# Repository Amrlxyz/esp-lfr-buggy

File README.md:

# ESP Line Following Robot

**GROUP 48:** 2nd Year Embedded Systems Project (ESP) 2023/24.

Project is in collaboration with 5 teammates: 
- [@Amrlxyz (me)](https://github.com/Amrlxyz) : Main Programmer + 3D CAD Designer 
- [@Hubr1z](https://github.com/Hubr1z) : 2nd Programmer
- [@Sarahelma](https://github.com/Sarahelma) : PCB Designer
- [@nishoujiwojiubuhuine](https://github.com/nishoujiwojiubuhuine) : 3rd Programmer + General Tech 
- [@Giselle-zheng](https://github.com/Giselle-zheng) : Wiring and Electrical

## Gallery

*Buggy Picture on the final race day*

*Final Buggy Render Using SolidWorks*

## Achievements

- **ESP 2023/24 Final Race Winner !!!**
- 100% for TDA (Techincal Demonstration A)
- 100% for TDB (Techincal Demonstration B)
- 100% for TDC (Techincal Demonstration C)

## Features

- Mbed v5.15
- Nucleo STM32F401RE 
- Custom Sensor Array PCB
- Array of 6x TCRT5000 IR sensor for line following
- Custom CAD Model Designed in Solidworks

## API Documentation

Link to documentation: [Github Pages](https://amrlxyz.github.io/esp-lfr-buggy/)

## How to Use

### Flashing the MCU

1. Use the wiring diagram to connect the components.
2. Clone the project directly to Keil Studio Cloud.
3. Compile and flash on to the microcontroller.
4. Control the buggy using Bluetooth commands.

### How to run

1. Connect BLE to a phone
2. Place the whole sensor array in the black area of the track
3. Send "calibrate" Command
4. Wait until message is recieved on the phone
5. Place the buggy in the middle of the line
6. Send "line_follow" Command

## Buggy Commands

### Setup

1. Use "Serial Bluetooth Terminal" app on Android
2. Settings -> Send -> Newline -> None
3. Send Commands

### Command Format 

[2/3 Capital Letters] [optional value for certain commands] ['/' -> end character]

Full command list is in main.cpp

__Examples:__

EC/ -> "Execute" "Calibrate"

EF/ -> "Execute" "line_follow"

GSB/ -> Get the speed of both motors

## Linkedin Article

[Article Link](https://www.linkedin.com/pulse/2nd-year-embedded-systems-project-final-race-winner-hakeem-jfuzf)

I might have mentioned a follow-up technical write-up at the end... but life (and distractions) keep happening. We'll see.

## Hello Future UoM 2nd Yr EEE Students

Feel free to use this code as inspiration (at your own risk). Looking back, definitely there are ways to improve it.

If you find the code helpful, feel free to drop a star ⭐ on the repo _(I crave external validation)_

Goodluck!

## Dependencies

Imported 3rd Party Mbed Libraries

- [Driver Board Onboard Battery Monitor](https://os.mbed.com/users/EmbeddedSam/code/Nucleo_F401RE_DS271_Battery_Monitor/) by Sam Walsh
- [QEI Library](https://os.mbed.com/cookbook/QEI) by Aron Berk

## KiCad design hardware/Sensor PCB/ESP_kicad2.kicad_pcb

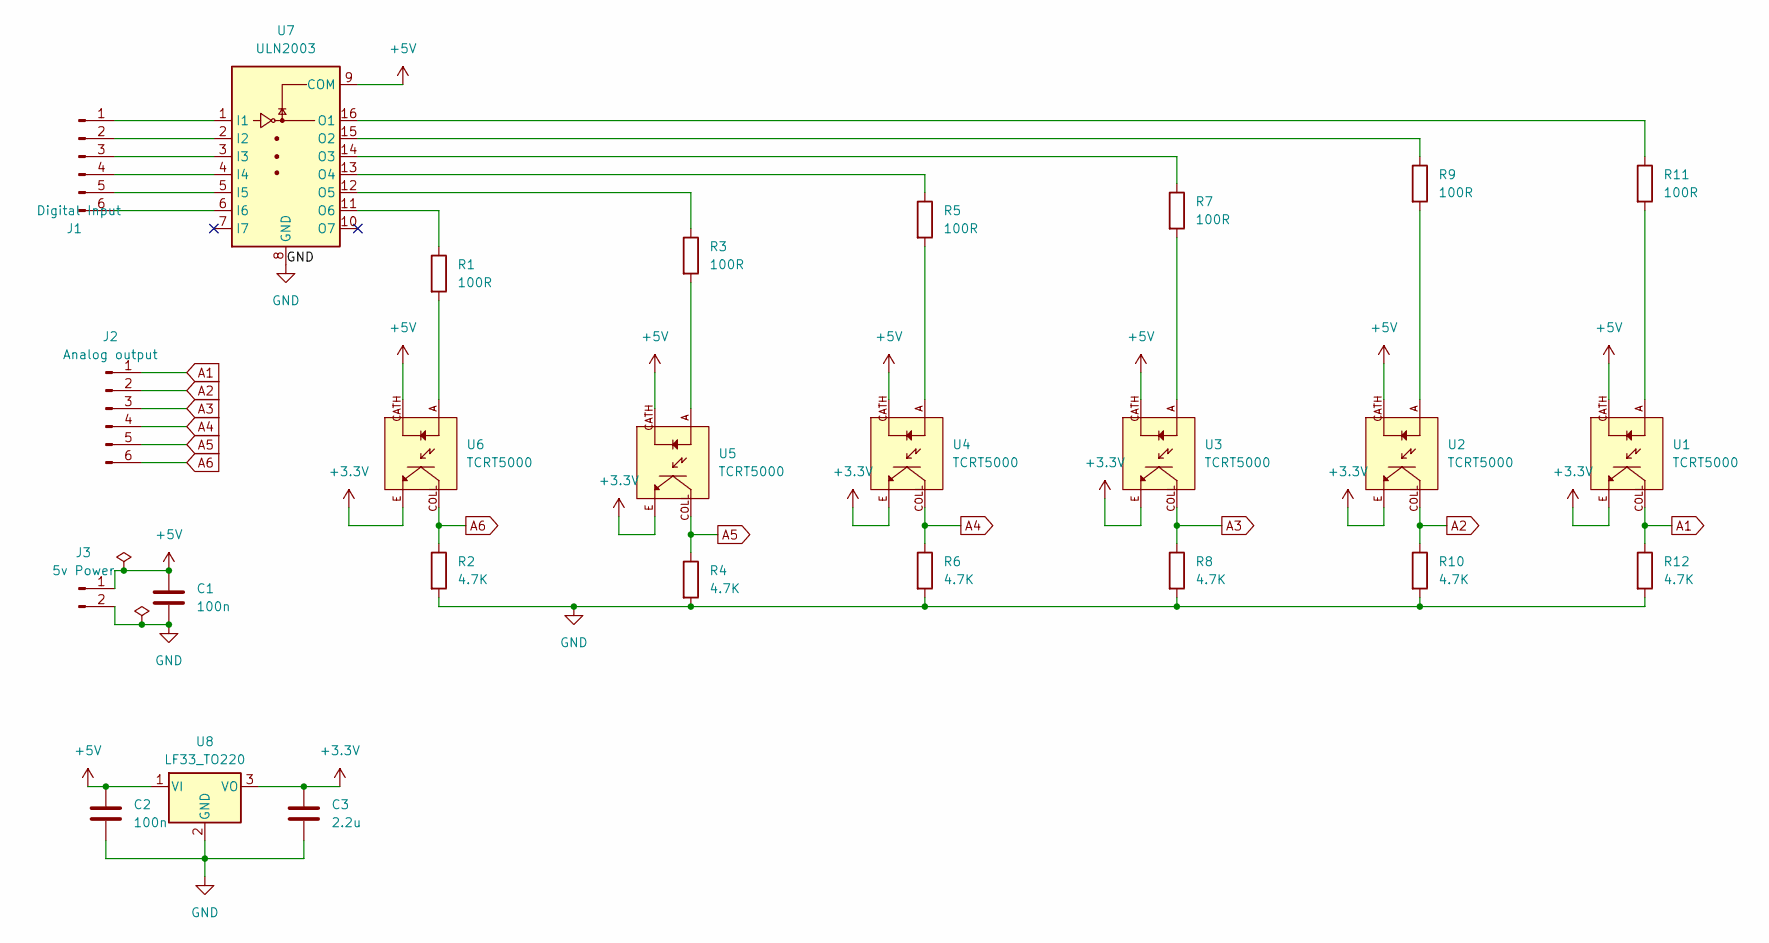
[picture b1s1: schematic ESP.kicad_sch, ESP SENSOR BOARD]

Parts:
C1, C2: 100n; CP_Radial_D5.0mm_P2.50mm
C3: 2.2u; CP_Radial_D5.0mm_P2.50mm
J1: Digital Input; JST_EH_B6B-EH-A_1x06_P2.50mm_Vertical
J2: Analog output; JST_EH_B6B-EH-A_1x06_P2.50mm_Vertical
J3: 5v Power; JST_ACH_BM02B-ACHSS-GAN-ETF_1x02-1MP_P1.20mm_Vertical
R1, R3, R5, R7, R9: 100R; R_Axial_DIN0207_L6.3mm_D2.5mm_P7.62mm_Horizontal
R2, R4, R6, R8, R10, R12: 4.7K; R_Axial_DIN0207_L6.3mm_D2.5mm_P7.62mm_Horizontal
R11: 100R; R_Axial_DIN0207_L6.3mm_D2.5mm_P5.08mm_Vertical
U1, U2, U3, U4, U5, U6: TCRT5000; OPTO_TCRT5000; PARTREV 1.7
U7: ULN2003; DIP-16_W7.62mm
U8: LF33_TO220; TO-220-3_Vertical

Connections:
+3.3V: C3.1, U1.E, U2.E, U3.E, U4.E, U5.E, U6.E, U8.3 (VO)
+5V: C1.1, C2.1, J3.1, U1.CATH, U2.CATH, U3.CATH, U4.CATH, U5.CATH, U6.CATH, U7.9 (COM), U8.1 (VI)
A1: J2.1, R12.1, U1.COLL
A2: J2.2, R10.1, U2.COLL
A3: J2.3, R8.1, U3.COLL
A4: J2.4, R6.1, U4.COLL
A5: J2.5, R4.1, U5.COLL
A6: J2.6, R2.1, U6.COLL
GND: C1.2, C2.2, C3.2, J3.2, R2.2, R4.2, R6.2, R8.2, R10.2, R12.2, U7.8 (GND), U8.2 (GND)
unnamed: J1.1, U7.1 (I1)
unnamed: J1.2, U7.2 (I2)
unnamed: J1.3, U7.3 (I3)
unnamed: J1.4, U7.4 (I4)
unnamed: J1.5, U7.5 (I5)
unnamed: J1.6, U7.6 (I6)
unnamed: R1.2, U6.A
unnamed: R3.2, U5.A
unnamed: R5.2, U4.A
unnamed: R7.2, U3.A
unnamed: R9.2, U2.A
unnamed: R11.2, U1.A
unnamed: R11.1, U7.16 (O1)
unnamed: R9.1, U7.15 (O2)
unnamed: R7.1, U7.14 (O3)
unnamed: R5.1, U7.13 (O4)
unnamed: R3.1, U7.12 (O5)
unnamed: R1.1, U7.11 (O6)

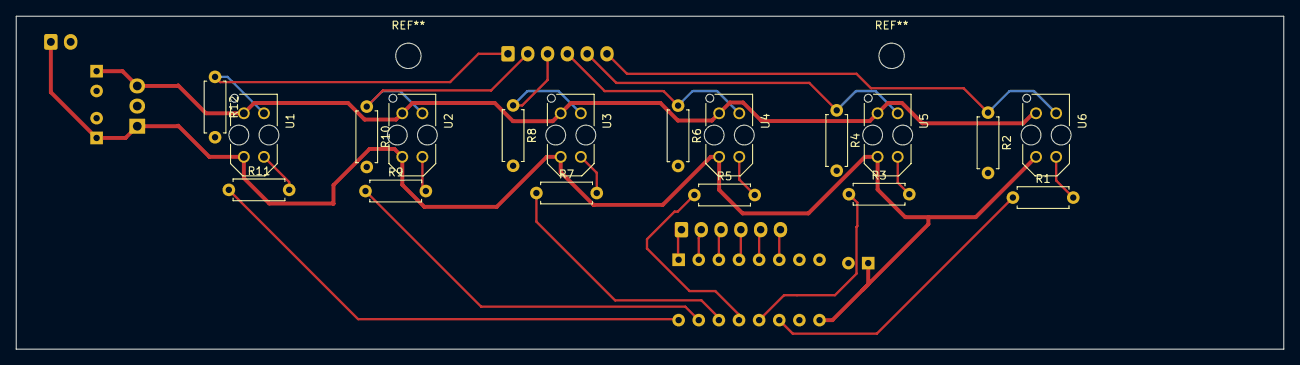
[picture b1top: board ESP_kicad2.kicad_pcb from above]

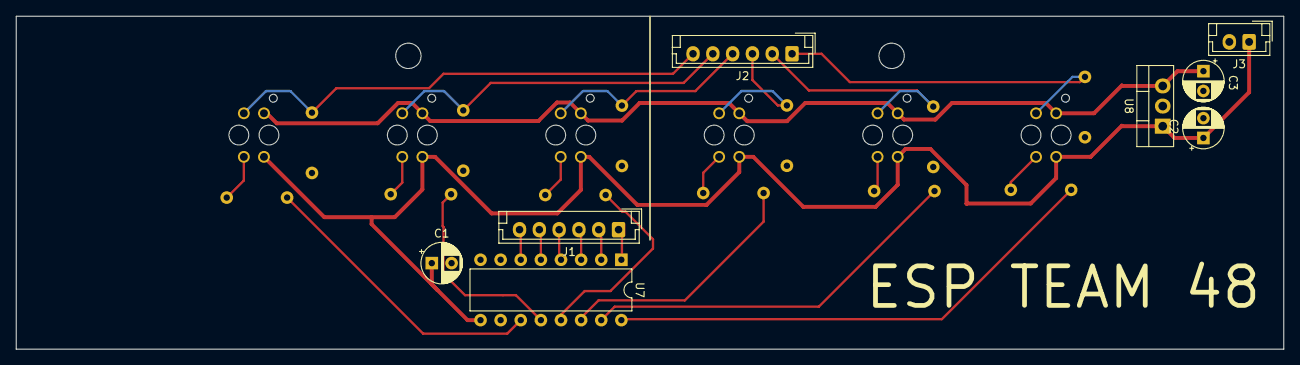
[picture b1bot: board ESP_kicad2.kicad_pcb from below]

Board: 2 copper layers, 160.0 x 42.0 mm, 26 parts (8 on the bottom side), 27 nets.

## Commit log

2024-02-11 First Commit - unfinished comments but the bluetooth works
2024-02-11 changed README file
2024-02-12 helloworld
2024-02-12 motor.h added
2024-02-13 added comments to bluetooth class. Added bluetooth command types.
2024-02-14 added command to read float value
2024-02-14 PID.h added
2024-02-14 lab work
2024-02-15 Updated to latest Pinouts, changed few bluetooth comments.
2024-02-16 Fixed formatting of header file and added seperate source cpp file
2024-02-16 edited gitignore
2024-02-16 Merging latest bluetooth to main and fixed conflicts
2024-02-16 added encoder class and few lines in main to test the encoder
2024-02-16 Fixed some stuff with timer
2024-02-17 fixed the formula for angle calculation
2024-02-17 Updated new pinouts for encoders
2024-02-17 added motor driver board class to control en pin, battery monitor is wip
2024-02-20 Finished bluetooth class parse data function. y in this branch? cuz Ican
2024-02-20 Theres going to be a lot of copy pasting ugly code to check all the case
2024-02-20 blueotooth command handling complete (for now) -hundreds of ugly code :(
2024-02-20 Changed the calculations to use ticker for consistent update frequency.
2024-02-20 structured the PID library
2024-02-20 Improved PID class and streamlined variable names
2024-02-20 made the framework to complete the square task. The logic is WIP
2024-02-20 Added few temporary lines for debugging PID and test other tasks
2024-02-22 seperated the classes into external header/source files
2024-02-22 bugfixes, added control for serial updates timing
2024-02-22 formatted the PC debug statements
2024-02-23 fixed small bugs with ticker not working
2024-02-23 created a simple code for square task wihout PID.
2024-02-23 changed to two wheel for turning in square test
2024-02-28 Lots of updates, motor/angle PID, low pass speed and other features.
2024-02-29 changed square task to use PID control
2024-02-29 small changes and cleaning the code
2024-02-29 more cleaning
2024-03-01 TDA code
2024-03-06 added sensor class
2024-03-07 added sensor stuff
2024-03-08 added led control and sampling average reading for the sensor class
2024-03-08 streamlined naming for sensor data members to 0 to 5
2024-03-10 combined and removed encoder/vp class. simplifictions of main.cpp
2024-03-11 added measurement of current and voltage of the board n reorganise
2024-03-12 bugfixes for the driverboard readings
2024-03-14 Post First Lab Code. Fixed bugs and speed limit to .9 DC
2024-03-26 code used for motor pid tuning
2024-04-01 Preparing for Documentation and TDB
2024-04-01 removed dependency of constants.h from motor.cpp
2024-04-01 small bt fix
2024-04-02 Added simple doxygen setup
2024-04-02 Setting up doxygen auto
2024-04-02 update to action to fupdate on TDB
2024-04-02 testing action
2024-04-02 testing action again
2024-04-02 fixed doxyfile config
2024-04-02 re-structuring docs
2024-04-02 starting documentation
2024-04-02 fixing github actions
2024-04-02 change action branch name
2024-04-02 testing actions
2024-04-02 Update Doxyfile
2024-04-02 removed local docs
2024-04-03 BIG CODE RESTRUCTURE. bt parse now in main. code simplifications.
2024-04-05 small reorganise and changed lp filter constants
2024-04-08 added comments, please go through them
2024-04-11 starting API documentation
2024-04-11 cleaning stuff up
2024-04-11 commented bluetooth and driverboard class
2024-04-11 Completed comments for documentations
2024-04-11 Finalising Readme file
2024-04-11 Finalised Readme file for doxygen
2024-04-11 Initializing gh-pages branch
2024-04-11 added doxygen docs
2024-04-11 added index redirection
2024-04-11 moved redirection indexhtml
2024-04-11 changed redirection
2024-04-11 testing redirection
2024-04-11 final redirect
2024-04-11 updated doxyfile
2024-04-11 finalised doxygen color
2024-04-11 update docs (color)
2024-04-11 moved index
2024-04-11 changed redirect url
2024-04-11 test with no files
2024-04-11 added back files
2024-04-12 reverting to a working code (hopefully)
2024-04-12 wrking tdb code as of friday
2024-04-12 working but the stop line is not consistent at track
2024-04-12 streamlined the sensor output
2024-04-17 tweaking the auto stop
2024-04-17 final tdb code cuz its working + goated
2024-04-17 works ok for now
2024-04-17 works better
2024-04-19 seperated Angle and Sensor PID
2024-04-24 Small Changes and stuff not really working
2024-04-24 Changes and prepped for max speed test
2024-04-25 idk whats going on
2024-04-25 few changes but still unstable
2024-04-25 NEED SENSOR PID TUNING. added a LP filter which idk might caused problem
2024-04-26 Added Bluetooth PID adjustment
2024-04-26 fixed bluetooth bugs
2024-04-26 added untested accel function and sensor calibration
2024-04-26 added all extra featrues but untested fully. 0.9ms max speed tested
2024-04-27 Added initial min n max calibration
2024-04-27 Sampling count = 1 and increased update rate to 2500 + logging dump
2024-04-27 switched to a new speed offset algorithm
2024-04-29 stable without weights at 1.8m/s
2024-04-29 testing faster latest with slow accel
2024-04-29 adding seperate sensor ISR update with double rate. works 2ms with tilt
2024-04-29 works great at 2 m/s. might need to tune autostop addded stop detect lnie mode
2024-04-29 works well with the values, new line detect function works super well
2024-04-29 Code day before tdc. Added incremental turn. Works with any batt.
2024-05-01 CODE USED FOR TDC
2024-05-01 moved sensor pid to correct ISR
2024-05-06 code used for Final Race. Added Turning feature when off line.
2024-06-11 updating the readme file post final race.
2024-06-11 fixed readme picture links
2024-06-11 updated to latest final race code
2024-06-11 github pages wont update
2025-04-30 added the python script for logging to the repo
2025-04-30 added all files related to the project as archive and updated README
